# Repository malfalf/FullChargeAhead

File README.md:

# FullChargeAhead
Cargador de baterias

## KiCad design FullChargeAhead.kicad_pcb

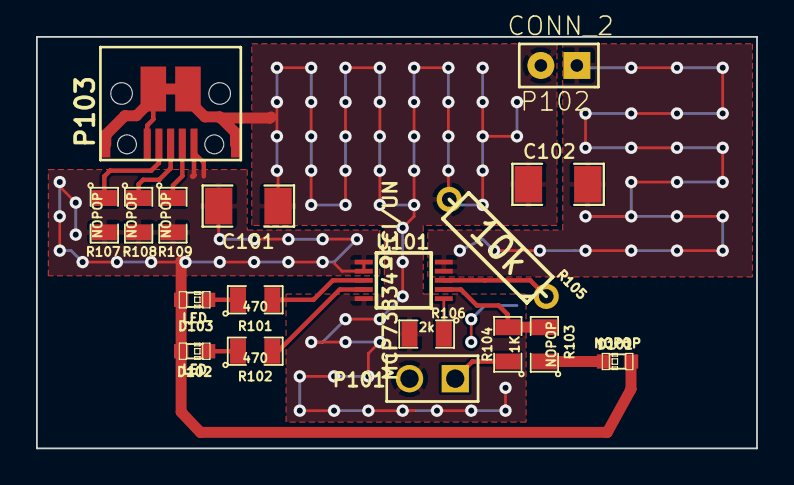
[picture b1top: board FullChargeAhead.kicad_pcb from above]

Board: 2 copper layers, 40.0 x 22.9 mm, 18 parts (0 on the bottom side), 15 nets.

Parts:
C101, C102: 4.7U; SM1206
D101: NOPOP; LED-0603
D102, D103: LED; LED-0603
P101: CONN_2; PIN_ARRAY_2X1
P102: CONN_2; JST_2_pin
P103: MICROUSB-B; USB_MICRO_B(10103594)v2
R101, R102: 470; SM0805
R103, R107, R108, R109: NOPOP; SM0805
R104: 1K; SM0805
R105: 10k; R3
R106: 2k; SM0805
U101: MCP73834-FCI/UN; MSOP10-0.5

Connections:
/Vbat: C102.1, P102.1, U101.9, U101.10
/Vdd: C101.1, D101.1, D102.1, D103.1, P103.1, R107.2, R108.2, R109.2, U101.1, U101.2
GND: C101.2, C102.2, P101.2, P102.2, P103.5, P103.7, P103.8, P103.9, R105.2, R106.2, U101.5
unnamed: P101.1, R104.1
unnamed: R105.1, U101.8
unnamed: R103.2, R104.2, U101.7
unnamed: P103.4, R107.1
unnamed: P103.3, R108.1
unnamed: R102.2, U101.4
unnamed: P103.2, R109.1
unnamed: D101.2, R103.1
unnamed: R101.2, U101.3
unnamed: R106.1, U101.6
unnamed: D102.2, R102.1
unnamed: D103.2, R101.1

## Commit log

2015-11-27 Creando el esquemático
2015-11-28 Did ERC check, annotated
2015-11-29 Creado footprint del micro USB y el layout
2015-11-29 Seguimos con el layout
2015-12-02 Finalizando el layout
2015-12-03 Acabando el layout, generando gerbers y placas pedidas
2015-12-11 Creada una primera versión del BOM
